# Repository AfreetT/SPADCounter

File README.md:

# SPADCounter

A simple pulse counter, based on a binary counter, for APDs like PerkinElmer/Excelitas single photon avalanche photodiodes. 
It can read the pulse train coming from the diode and communicate with a PC, granting a simple interface to track the photon counts.
It also controls the power supply to the diode (a simple pass-through with some transistors), to avoid diode damage due to overexposure.
It is programmed to trigger at 1 Mcps, but the threshold is programmable. 
Everything can be controlled via a simple serial interface (diode on/off commands, getting counts and setting the threshold value).

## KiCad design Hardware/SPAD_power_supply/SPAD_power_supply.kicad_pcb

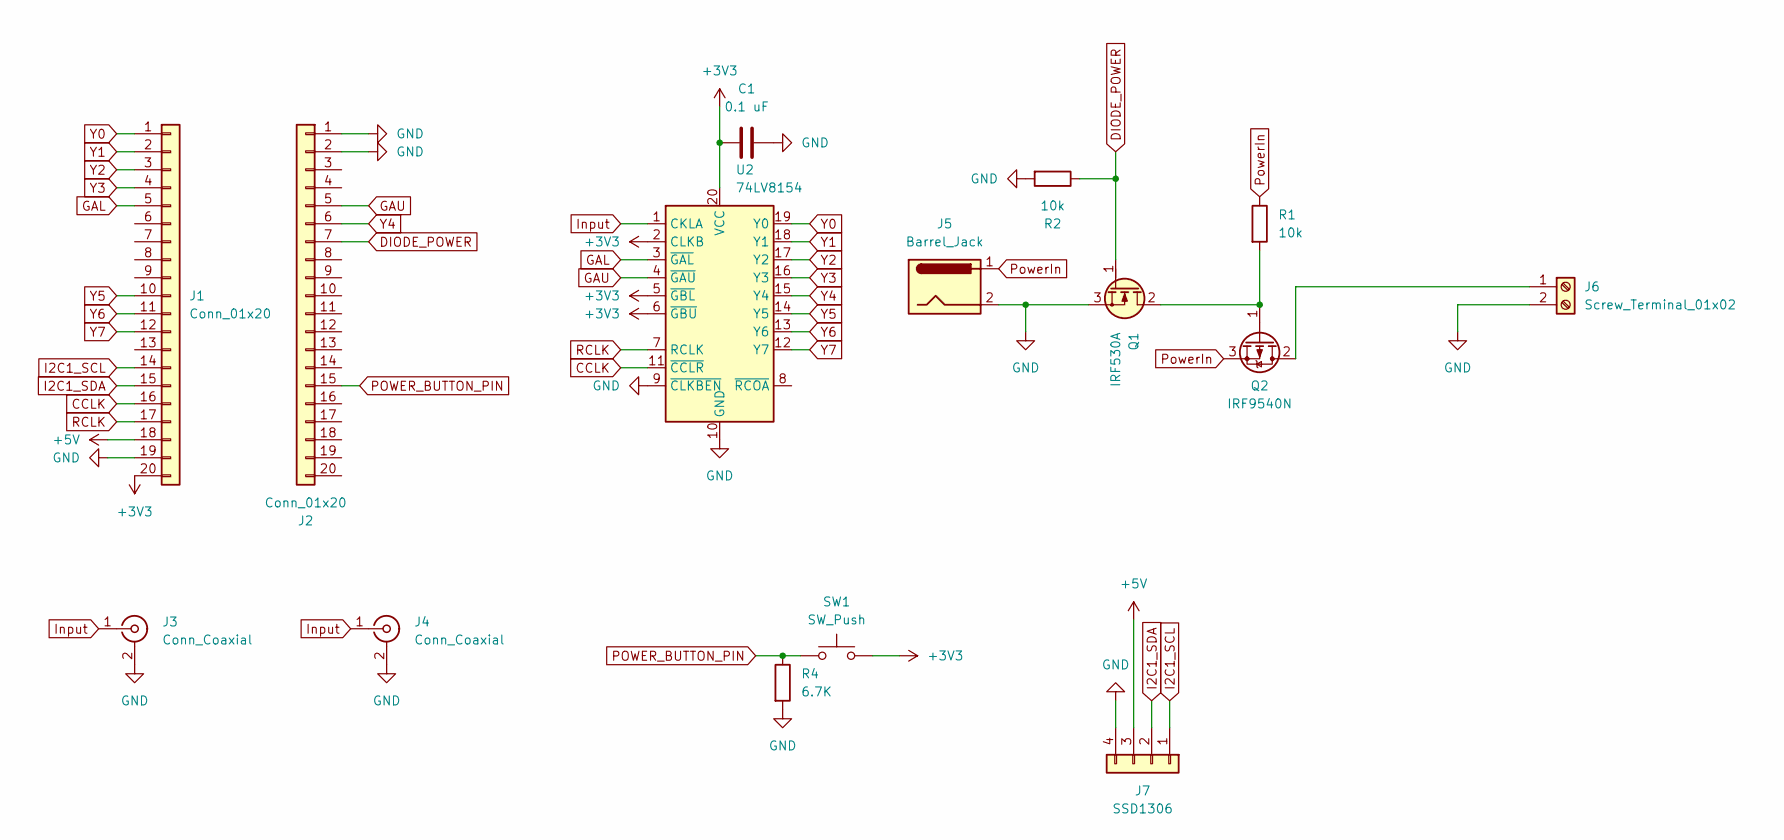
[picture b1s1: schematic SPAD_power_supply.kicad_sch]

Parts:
C1: 0.1 uF; C_Disc_D4.3mm_W1.9mm_P5.00mm
J1, J2: Conn_01x20; PinSocket_1x20_P2.54mm_Vertical
J3, J4: Conn_Coaxial; BNC_Amphenol_B6252HB-NPP3G-50_Horizontal
J5: Barrel_Jack; BarrelJack_CUI_PJ-063AH_Horizontal
J6: Screw_Terminal_01x02; TerminalBlock_CUI_TB007-508-02_1x02_P5.08mm_Horizontal
J7: SSD1306; PinHeader_1x04_P2.54mm_Vertical
Q1: IRF530A; TO-220-3_Vertical_GDS
Q2: IRF9540N; TO-220-3_Vertical
R1, R2: 10k; R_Axial_DIN0204_L3.6mm_D1.6mm_P5.08mm_Horizontal
R4: 6.7K; R_Axial_DIN0204_L3.6mm_D1.6mm_P5.08mm_Horizontal
SW1: SW_Push; SW_PUSH_6mm_H8mm
U2: 74LV8154; DIP-20_W7.62mm_Socket

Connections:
+3V3: C1.1, J1.20, SW1.2, U2.2 (CLKB), U2.5 (~GBL), U2.6 (~GBU), U2.20 (VCC)
+5V: J1.18, J7.3
CCLK: J1.16, U2.11 (~CCLR)
DIODE_POWER: J2.7, Q1.1 (G), R2.1
GAL: J1.5, U2.3 (~GAL)
GAU: J2.5, U2.4 (~GAU)
GND: C1.2, J1.19, J2.1, J2.2, J3.2 (Ext), J4.2 (Ext), J5.2, J6.2, J7.4, Q1.3 (S), R2.2, R4.2, U2.9 (~CLKBEN), U2.10 (GND)
I2C1_SCL: J1.14, J7.1
I2C1_SDA: J1.15, J7.2
Input: J3.1 (In), J4.1 (In), U2.1 (CKLA)
unnamed: J6.1, Q2.2 (D)
unnamed: Q1.2 (D), Q2.1 (G), R1.2
POWER_BUTTON_PIN: J2.15, R4.1, SW1.1
PowerIn: J5.1, Q2.3 (S), R1.1
RCLK: J1.17, U2.7 (RCLK)
Y0: J1.1, U2.19 (Y0)
Y1: J1.2, U2.18 (Y1)
Y2: J1.3, U2.17 (Y2)
Y3: J1.4, U2.16 (Y3)
Y4: J2.6, U2.15 (Y4)
Y5: J1.10, U2.14 (Y5)
Y6: J1.11, U2.13 (Y6)
Y7: J1.12, U2.12 (Y7)

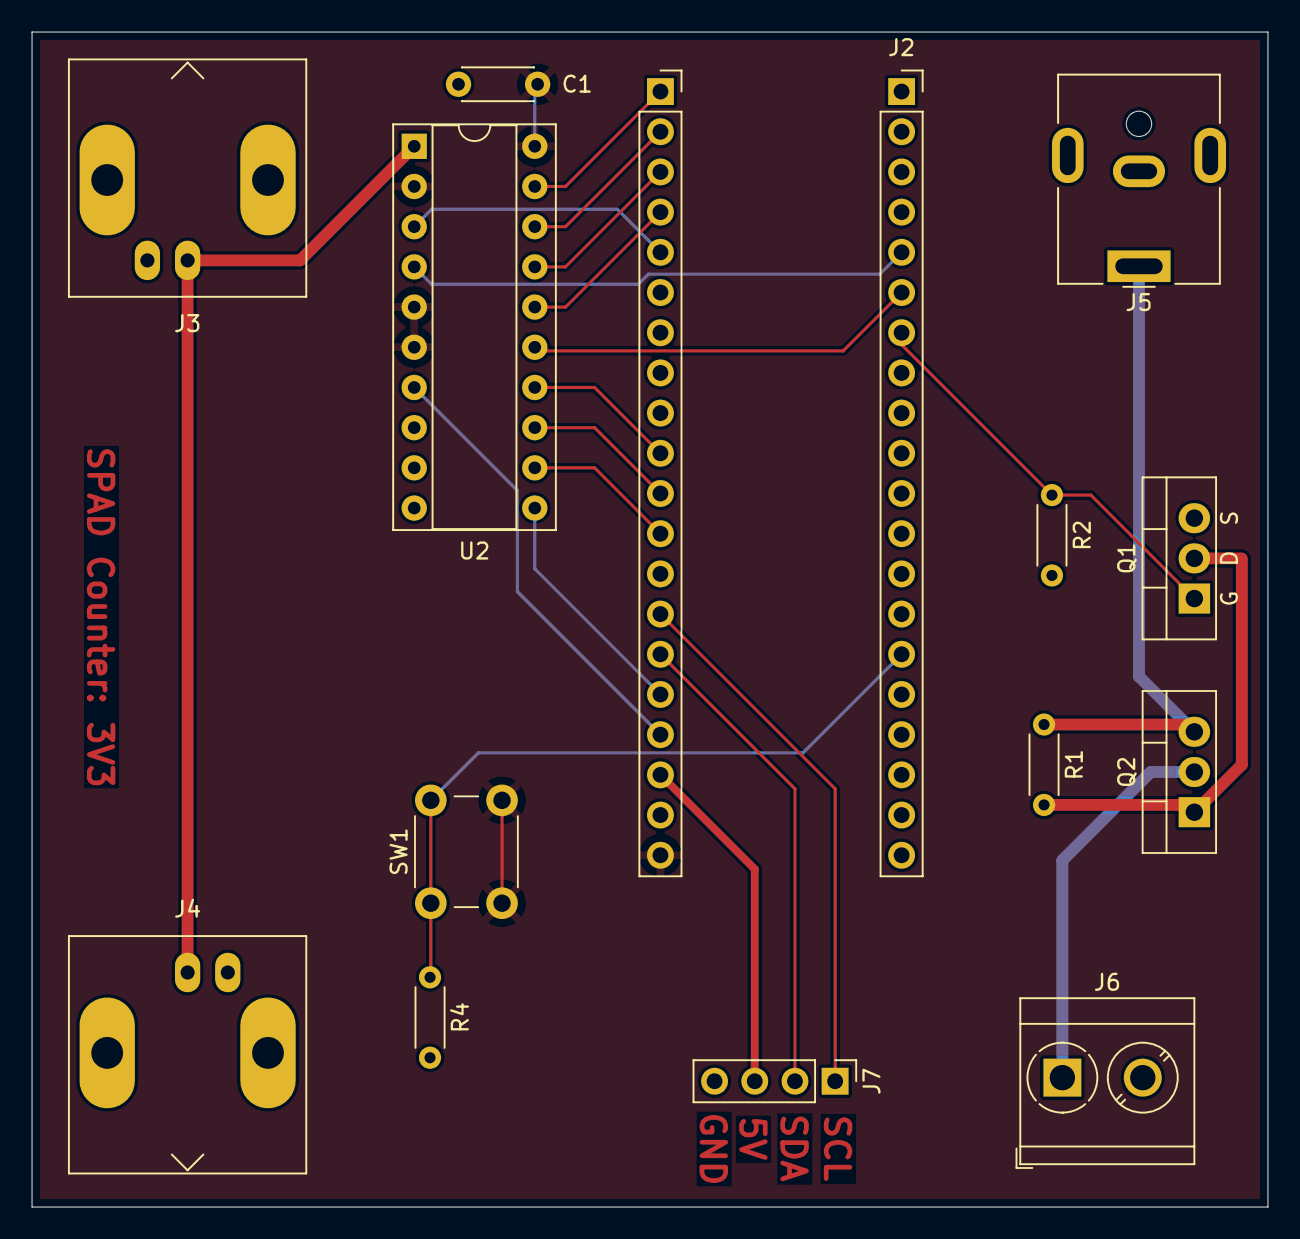
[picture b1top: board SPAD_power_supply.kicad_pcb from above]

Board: 2 copper layers, 78.1 x 74.2 mm, 15 parts (0 on the bottom side), 23 nets.

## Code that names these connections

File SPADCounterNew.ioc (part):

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Mcu.Name=STM32F103C(8-B)Tx
Mcu.Package=LQFP48
Mcu.UserName=STM32F103C8Tx
PA1.GPIOParameters=GPIO_PuPd,GPIO_Label
PA1.GPIO_Label=POWER_BUTTON_PIN
PA1.GPIO_PuPd=GPIO_PULLUP
PA1.Signal=GPIO_Input
PA11.Mode=Device
PA11.Signal=USB_DM
PA12.Mode=Device
PA12.Signal=USB_DP
PA13.Mode=Serial_Wire
PA13.Signal=SYS_JTMS-SWDIO
PA14.Mode=Serial_Wire
PA14.Signal=SYS_JTCK-SWCLK
PA15.GPIOParameters=GPIO_Label,GPIO_Mode
PA15.GPIO_Label=Y5
PA15.GPIO_Mode=GPIO_MODE_INPUT
PA15.Signal=GPIO_Input
PA8.GPIOParameters=GPIO_Label
PA8.GPIO_Label=GAL
PA8.Signal=GPIO_Output
PB1.GPIOParameters=GPIO_Label
PB1.GPIO_Label=DIODE_POWER
PB1.Signal=GPIO_Output
PB10.GPIOParameters=GPIO_Label,GPIO_Mode
PB10.GPIO_Label=Y4
PB10.GPIO_Mode=GPIO_MODE_INPUT
PB10.Signal=GPIO_Input
PB11.GPIOParameters=GPIO_Label
PB11.GPIO_Label=GAU
PB11.Signal=GPIO_Output
PB12.GPIOParameters=GPIO_Label,GPIO_Mode
PB12.GPIO_Label=Y0
PB12.GPIO_Mode=GPIO_MODE_INPUT
PB12.Signal=GPIO_Input
PB13.GPIOParameters=GPIO_Label,GPIO_Mode
PB13.GPIO_Label=Y1
PB13.GPIO_Mode=GPIO_MODE_INPUT
PB13.Signal=GPIO_Input
PB14.GPIOParameters=GPIO_Label,GPIO_Mode
PB14.GPIO_Label=Y2
PB14.GPIO_Mode=GPIO_MODE_INPUT
PB14.Signal=GPIO_Input
PB15.GPIOParameters=GPIO_Label,GPIO_Mode
PB15.GPIO_Label=Y3
PB15.GPIO_Mode=GPIO_MODE_INPUT
PB15.Signal=GPIO_Input
PB3.GPIOParameters=GPIO_Label,GPIO_Mode
PB3.GPIO_Label=Y6
PB3.GPIO_Mode=GPIO_MODE_INPUT
PB3.Signal=GPIO_Input
PB4.GPIOParameters=GPIO_Label,GPIO_Mode
PB4.GPIO_Label=Y7
PB4.GPIO_Mode=GPIO_MODE_INPUT
PB4.Signal=GPIO_Input
PB6.Mode=I2C
PB6.Signal=I2C1_SCL
PB7.Mode=I2C
PB7.Signal=I2C1_SDA
PB8.GPIOParameters=GPIO_Label
PB8.GPIO_Label=CCLR
PB8.Signal=GPIO_Output
PB9.GPIOParameters=GPIO_Label
PB9.GPIO_Label=RCLK
PB9.Signal=GPIO_Output
PD0-OSC_IN.Mode=HSE-External-Oscillator
PD0-OSC_IN.Signal=RCC_OSC_IN
PD1-OSC_OUT.Mode=HSE-External-Oscillator
PD1-OSC_OUT.Signal=RCC_OSC_OUT
RCC.SYSCLKFreq_VALUE=72000000
RCC.SYSCLKSource=RCC_SYSCLKSOURCE_PLLCLK
board=custom
